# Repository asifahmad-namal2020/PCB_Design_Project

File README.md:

# PCB_Design_Project
PCB of three phase inverter designed by Engr. Asif Ahmad

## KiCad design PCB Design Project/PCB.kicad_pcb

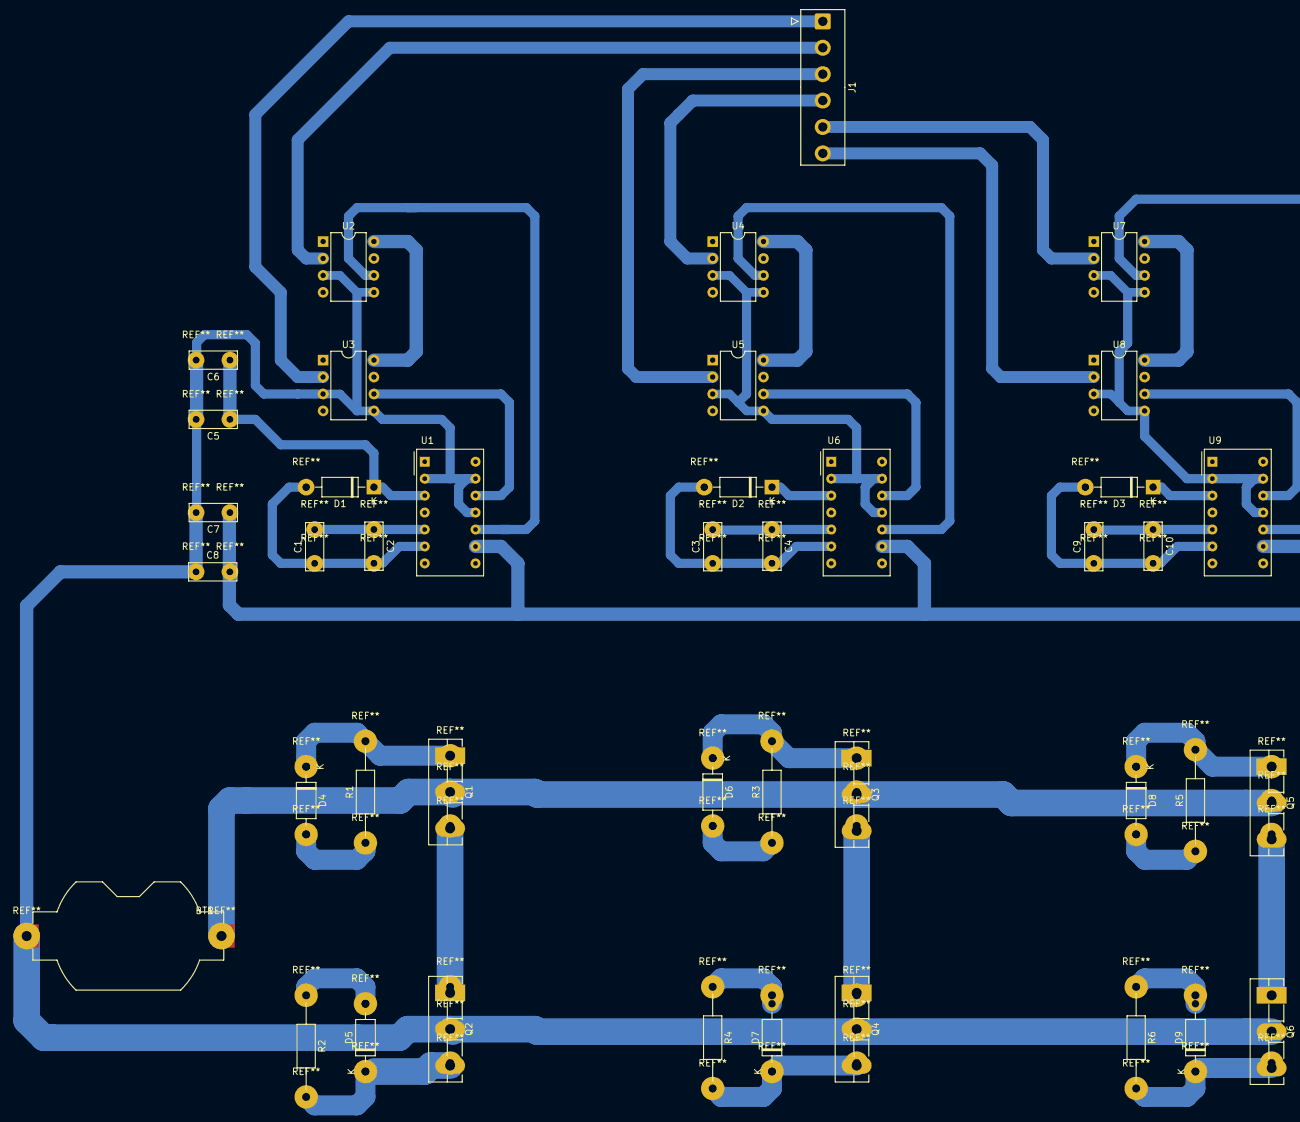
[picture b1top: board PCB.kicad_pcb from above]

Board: 2 copper layers, 42 parts (0 on the bottom side), 35 nets.

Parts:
BT1: Battery_Cell; BatteryHolder_Keystone_1058_1x2032
C1, C3, C5, C7, C9: CP1; C_Disc_D7.0mm_W2.5mm_P5.00mm
C2, C4, C6, C8, C10: C_Small; C_Disc_D7.0mm_W2.5mm_P5.00mm
D1, D2, D3, D4, D5, D6, D7, D8, D9: DIODE; D_DO-41_SOD81_P10.16mm_Horizontal
J1: Screw_Terminal_01x06; TE_826576-6_1x06_P3.96mm_Vertical
Q1, Q2, Q3, Q4, Q5, Q6: IRF6641; TO-3PB-3_Vertical
R1, R2, R3, R4, R5, R6: R; R_Axial_DIN0207_L6.3mm_D2.5mm_P15.24mm_Horizontal
U1, U6, U9: IR2110; MAN73A
U2, U3, U4, U5, U7, U8: TLP250; DIP-8_W7.62mm

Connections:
GND: BT1.2, C5.2, C6.2, C7.2, C8.1, Q2.2, Q4.2, Q6.2, U1.2, U1.11, U1.13, U2.3, U2.5, U3.3, U3.5, U4.3, U4.5, U5.3, U5.5, U6.2, U6.11, U6.13, U7.3, U7.5, U8.3, U8.5, U9.2, U9.11, U9.13
unnamed: BT1.1, Q1.2, Q3.2, Q5.2
unnamed: C1.1, C2.2, D1.2, U1.6
unnamed: C1.2, C2.1, Q1.3, Q2.1, U1.5
unnamed: C3.1, C4.2, D2.2, U6.6
unnamed: C3.2, C4.1, Q3.3, Q4.1, U6.5
unnamed: C5.1, C6.1, D1.1, D2.1, D3.1, U1.3, U6.3, U9.3
unnamed: C7.1, C8.2, U1.9, U6.9, U9.9
unnamed: C9.2, C10.1, Q5.3, Q6.1, U9.5
unnamed: C9.1, C10.2, D3.2, U9.6
unnamed: D4.1, Q1.1, R1.2
unnamed: D4.2, R1.1, U1.7
unnamed: D5.1, Q2.3, R2.2
unnamed: D5.2, R2.1, U1.1
unnamed: D6.1, Q3.1, R3.2
unnamed: D6.2, R3.1, U6.7
unnamed: D7.1, Q4.3, R4.2
unnamed: D7.2, R4.1, U6.1
unnamed: D8.1, Q5.1, R5.2
unnamed: D8.2, R5.1, U9.7
unnamed: D9.1, Q6.3, R6.2
unnamed: D9.2, R6.1, U9.1
unnamed: J1.1, U3.2
unnamed: J1.2, U2.2
unnamed: J1.3, U5.2
unnamed: J1.4, U4.2
unnamed: J1.5, U7.2
unnamed: J1.6, U8.2
unnamed: U1.10, U2.6
unnamed: U1.12, U3.6
unnamed: U2.8, U3.8, U4.8, U5.8, U7.8, U8.8
unnamed: U4.6, U6.10
unnamed: U5.6, U6.12
unnamed: U7.6, U9.10
unnamed: U8.6, U9.12

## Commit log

2022-07-08 PCB of three phase inverter
